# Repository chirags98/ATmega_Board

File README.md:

# ATmega_Board
This is a design to create a general purpose uC board using a ATmega328p microcontroller

Find the BOM (Bill of materials) on https://drive.google.com/open?id=1ma9ChhY5GpuYgg1Ucf6gE6C5UKoa5oTefCcq_7sxWGw

Find the Documentation of the board on https://drive.google.com/open?id=1ZgfvmyehAIBZDk0_nPWmhZg0xXYO81bvEzHlQfDXWbA

Find the example codes on https://github.com/chirags98/ATmega328-Example-Codes

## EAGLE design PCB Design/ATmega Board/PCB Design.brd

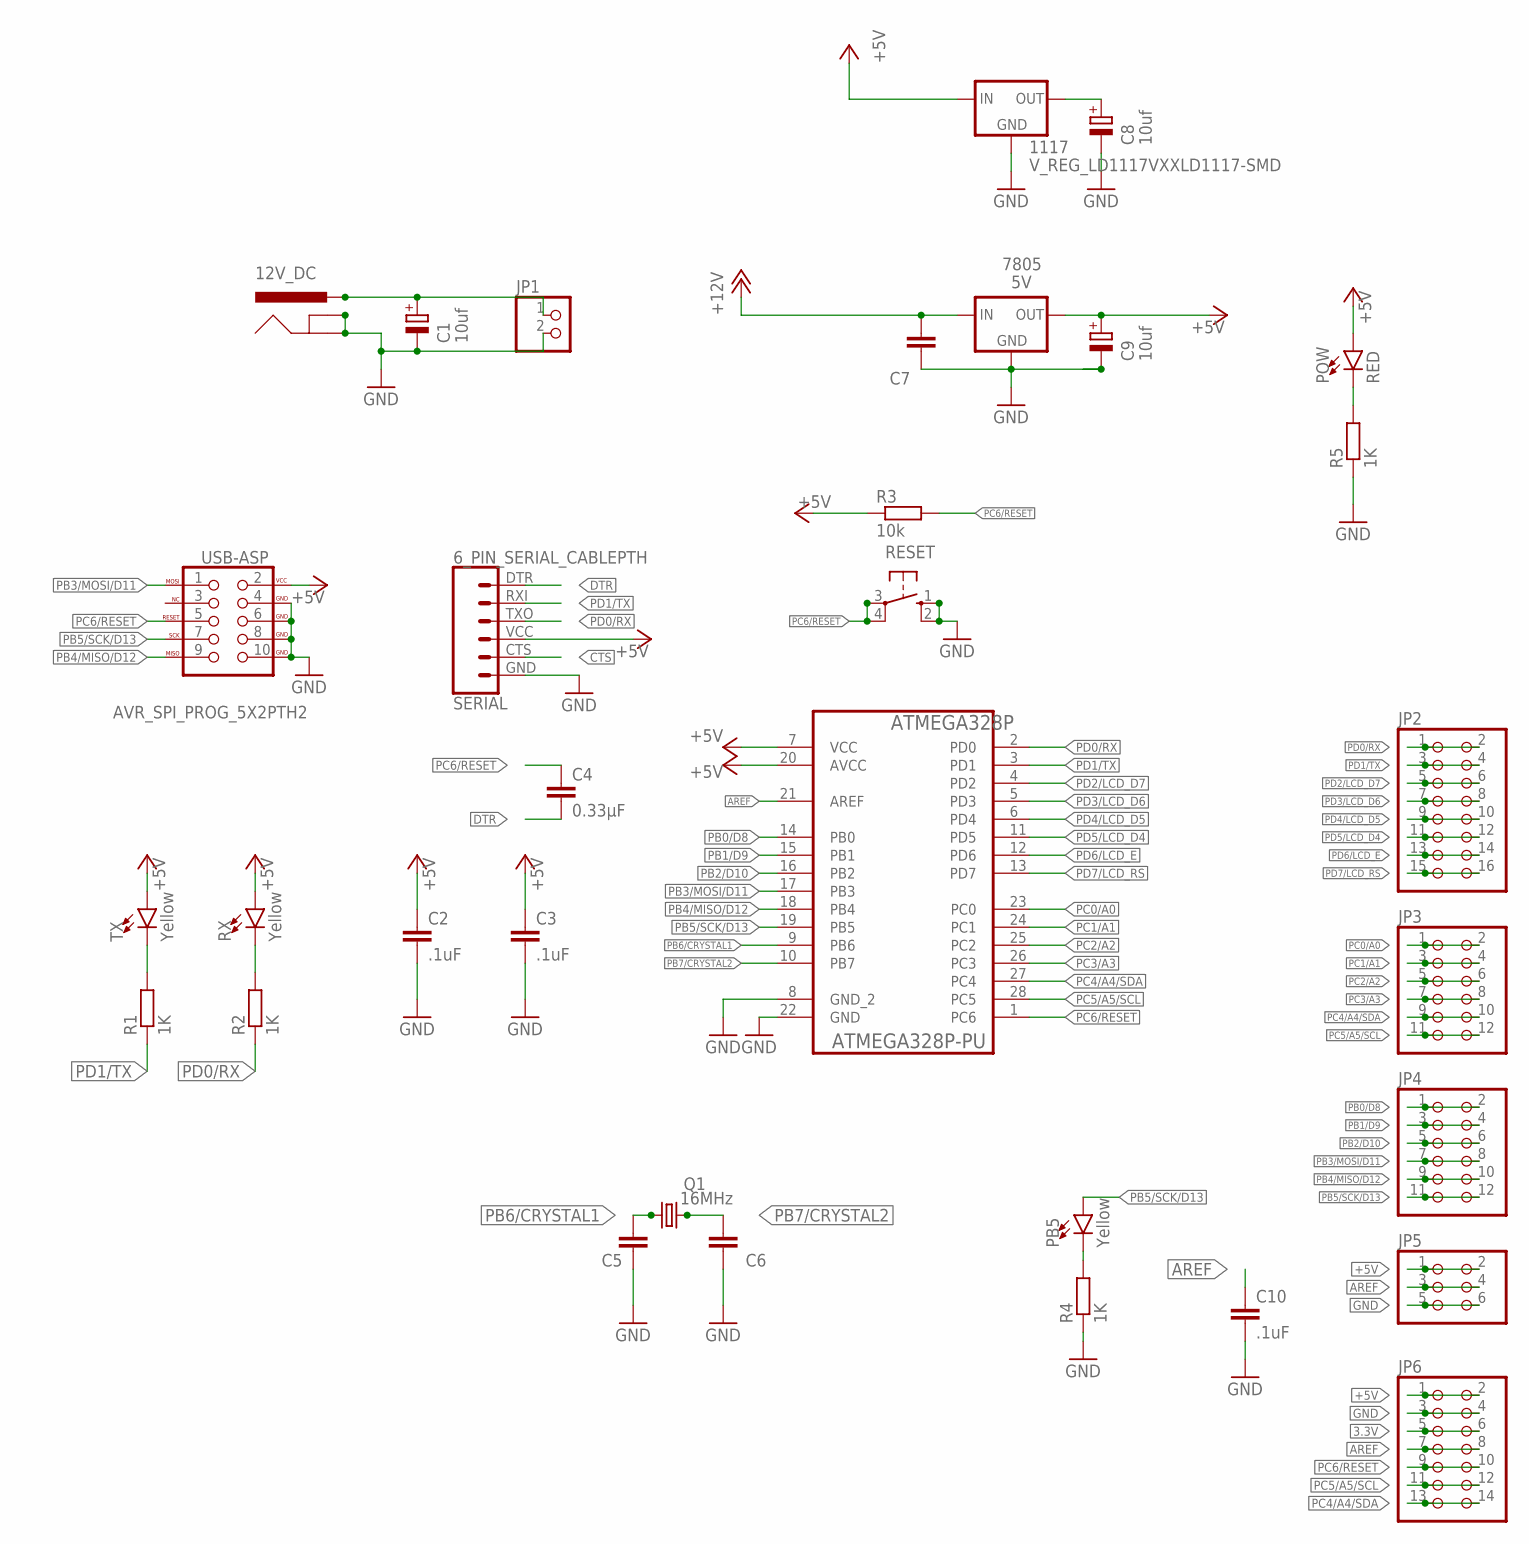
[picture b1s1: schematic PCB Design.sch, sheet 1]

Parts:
12V_DC: POWER_JACK; POWER_JACK_PTH; MPN SPC21365
1117: V_REG_LD1117VXXLD1117-SMD; SOT223
7805: 5V; TO-252
ATMEGA328P: ATMEGA328P-PU; DIP254P762X457-28
C1, C8, C9: 10uf; E2,5-6
C2, C3, C10: .1uF; C0805K
C4: 0.33µF; C0805K
C5, C6: 22pF; C0805K
C7: .1uf; C0805K
JP1: PINHD-1X2; 1X02
JP2: PINHD-2X8; 2X08
JP3, JP4: PINHD-2X6; 2X06
JP5: PINHD-2X3; 2X03
JP6: PINHD-2X7; 2X07
PB5: Yellow; LED-0603
POW: RED; LED-0603
Q1: 16MHz; HC49U70
R1, R2, R4, R5: 1K; M0805
R3: 10k; M0805
RESET: 10-XX; B3F-10XX
RX: Yellow; LED-0603
SERIAL: 6_PIN_SERIAL_CABLEPTH; FTDI_BASIC
TX: Yellow; LED-0603
USB-ASP: AVR_SPI_PROG_5X2PTH2; 2X5-SHROUDED

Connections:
3.3V: 1117.2 (OUT), C8.+, JP6.5, JP6.6
+5V: 1117.3 (IN), 7805.2 (OUT), ATMEGA328P.7 (VCC), ATMEGA328P.20 (AVCC), C2.1, C3.1, C9.+, JP5.1, JP5.2, JP6.1, JP6.2, POW.A, R3.1, RX.A, SERIAL.VCC (4), TX.A, USB-ASP.2 (VCC); also elsewhere on the board
+12V: 12V_DC.PWR, 7805.1 (IN), C1.+, C7.1, JP1.1
AREF: ATMEGA328P.21 (AREF), C10.1, JP5.3, JP5.4, JP6.7, JP6.8
CTS: SERIAL.CTS (5)
DTR: C4.2, SERIAL.DTR (1)
GND: 12V_DC.GND, 12V_DC.GNDBREAK, 1117.1 (GND), 7805.3 (GND), ATMEGA328P.8 (GND_2), ATMEGA328P.22 (GND), C1.-, C2.2, C3.2, C5.1, C6.1, C7.2, C8.-, C9.-, C10.2, JP1.2, JP5.5, JP5.6, JP6.3, JP6.4, R4.1, R5.1, RESET.1 (S), RESET.2 (S1), SERIAL.GND (6), USB-ASP.4 (GND), USB-ASP.6 (GND), USB-ASP.8 (GND), USB-ASP.10 (GND); also elsewhere on the board
unnamed: PB5.C, R4.2
unnamed: POW.C, R5.2
unnamed: R2.2, RX.C
unnamed: R1.2, TX.C
PB0/D8: ATMEGA328P.14 (PB0), JP4.1, JP4.2
PB1/D9: ATMEGA328P.15 (PB1), JP4.3, JP4.4
PB2/D10: ATMEGA328P.16 (PB2), JP4.5, JP4.6
PB3/MOSI/D11: ATMEGA328P.17 (PB3), JP4.7, JP4.8, USB-ASP.1 (MOSI)
PB4/MISO/D12: ATMEGA328P.18 (PB4), JP4.9, JP4.10, USB-ASP.9 (MISO)
PB5/SCK/D13: ATMEGA328P.19 (PB5), JP4.11, JP4.12, PB5.A, USB-ASP.7 (SCK)
PB6/CRYSTAL1: ATMEGA328P.9 (PB6), C5.2, Q1.1
PB7/CRYSTAL2: ATMEGA328P.10 (PB7), C6.2, Q1.2
PC0/A0: ATMEGA328P.23 (PC0), JP3.1, JP3.2
PC1/A1: ATMEGA328P.24 (PC1), JP3.3, JP3.4
PC2/A2: ATMEGA328P.25 (PC2), JP3.5, JP3.6
PC3/A3: ATMEGA328P.26 (PC3), JP3.7, JP3.8
PC4/A4/SDA: ATMEGA328P.27 (PC4), JP3.9, JP3.10, JP6.13, JP6.14
PC5/A5/SCL: ATMEGA328P.28 (PC5), JP3.11, JP3.12, JP6.11, JP6.12
PC6/RESET: ATMEGA328P.1 (PC6), C4.1, JP6.9, JP6.10, R3.2, RESET.3, RESET.4 (P1), USB-ASP.5 (RESET)
PD0/RX: ATMEGA328P.2 (PD0), JP2.1, JP2.2, R2.1, SERIAL.TXO (3)
PD1/TX: ATMEGA328P.3 (PD1), JP2.3, JP2.4, R1.1, SERIAL.RXI (2)
PD2/LCD_D7: ATMEGA328P.4 (PD2), JP2.5, JP2.6; also elsewhere on the board
PD3/LCD_D6: ATMEGA328P.5 (PD3), JP2.7, JP2.8; also elsewhere on the board
PD4/LCD_D5: ATMEGA328P.6 (PD4), JP2.9, JP2.10; also elsewhere on the board
PD5/LCD_D4: ATMEGA328P.11 (PD5), JP2.11, JP2.12; also elsewhere on the board
PD6/LCD_E: ATMEGA328P.12 (PD6), JP2.13, JP2.14; also elsewhere on the board
PD7/LCD_RS: ATMEGA328P.13 (PD7), JP2.15, JP2.16; also elsewhere on the board

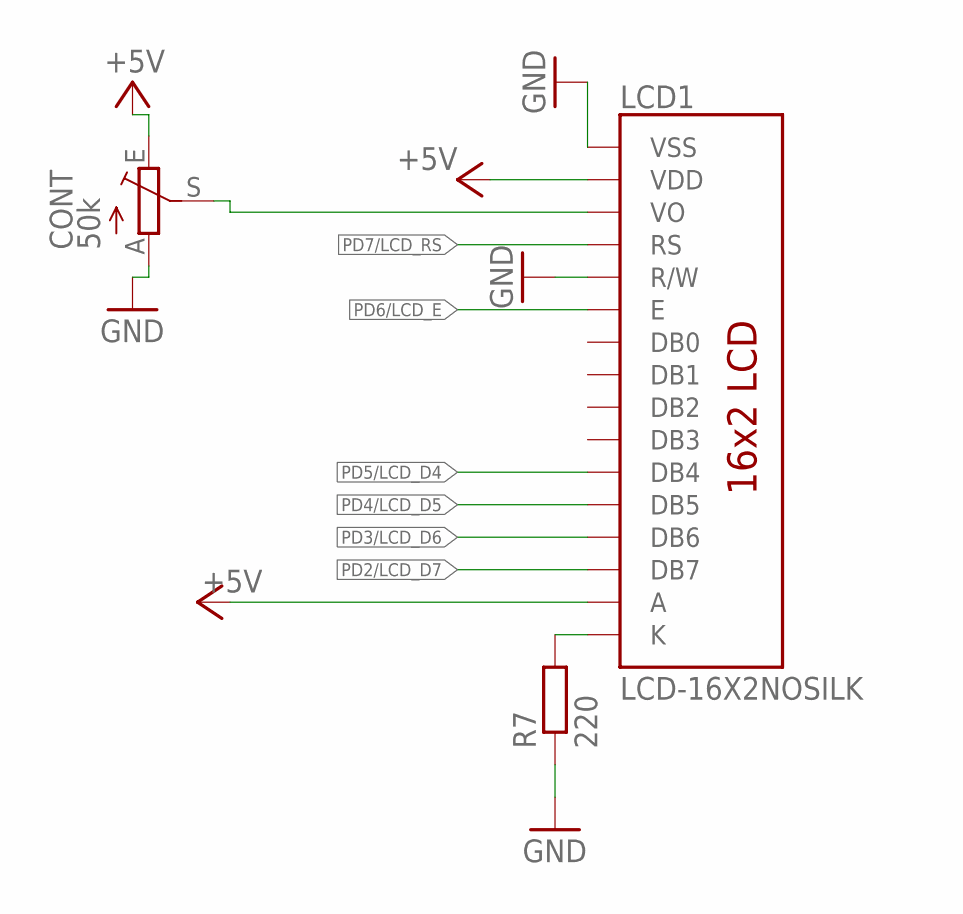
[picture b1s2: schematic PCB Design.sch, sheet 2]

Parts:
CONT: 50k; S64W
LCD1: LCD-16X2NOSILK; LCD-16X2_NOSILK
R7: 220; M0805

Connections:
+5V: CONT.E, LCD1.2 (VDD), LCD1.15 (A); also elsewhere on the board
GND: CONT.A, LCD1.1 (VSS), LCD1.5 (R/W), R7.1; also elsewhere on the board
unnamed: CONT.S, LCD1.3 (VO)
unnamed: LCD1.16 (K), R7.2
PD2/LCD_D7: LCD1.14 (DB7); also elsewhere on the board
PD3/LCD_D6: LCD1.13 (DB6); also elsewhere on the board
PD4/LCD_D5: LCD1.12 (DB5); also elsewhere on the board
PD5/LCD_D4: LCD1.11 (DB4); also elsewhere on the board
PD6/LCD_E: LCD1.6 (E); also elsewhere on the board
PD7/LCD_RS: LCD1.4 (RS); also elsewhere on the board

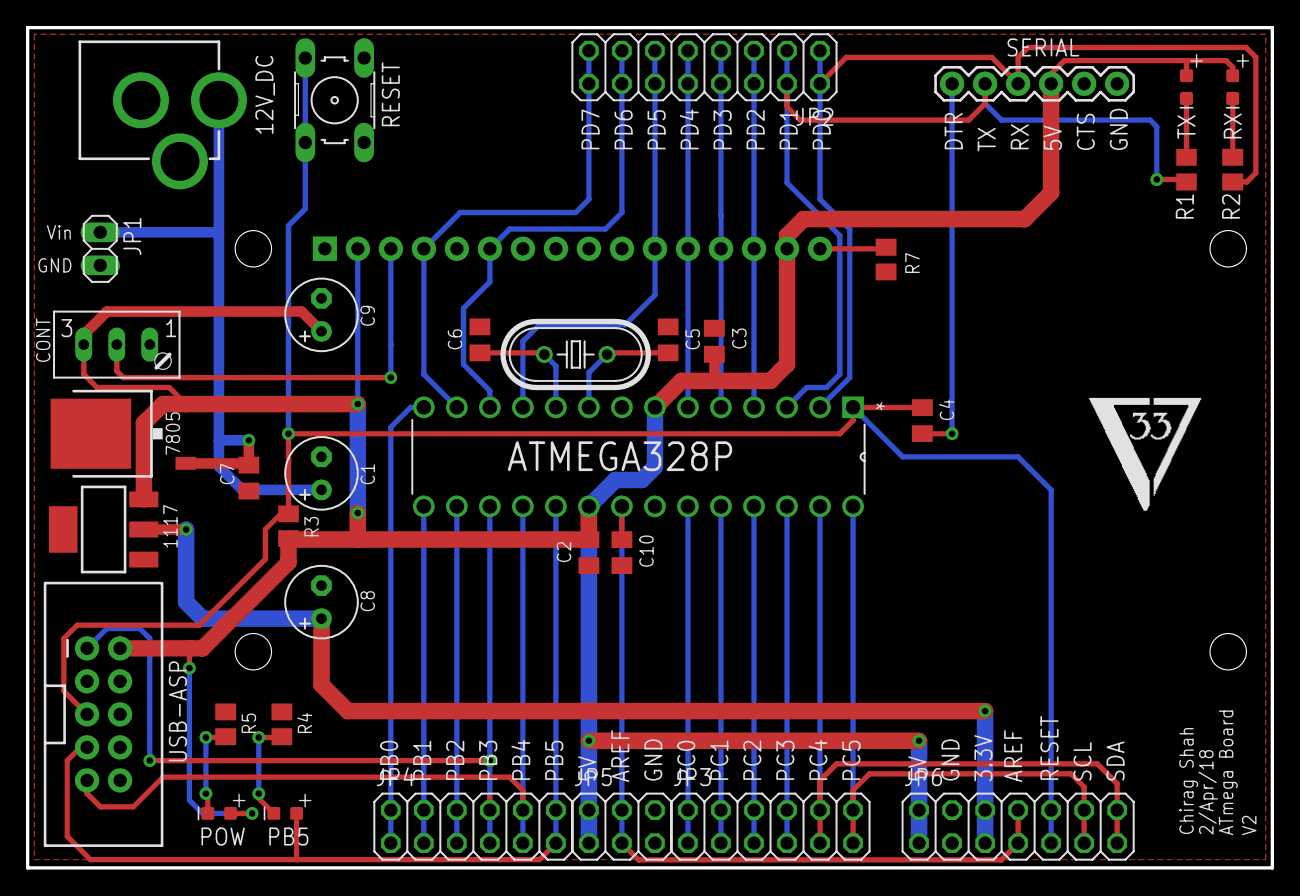
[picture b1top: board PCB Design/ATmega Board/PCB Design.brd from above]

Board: 2 copper layers, 95.8 x 64.6 mm, 36 parts (0 on the bottom side), 35 nets.

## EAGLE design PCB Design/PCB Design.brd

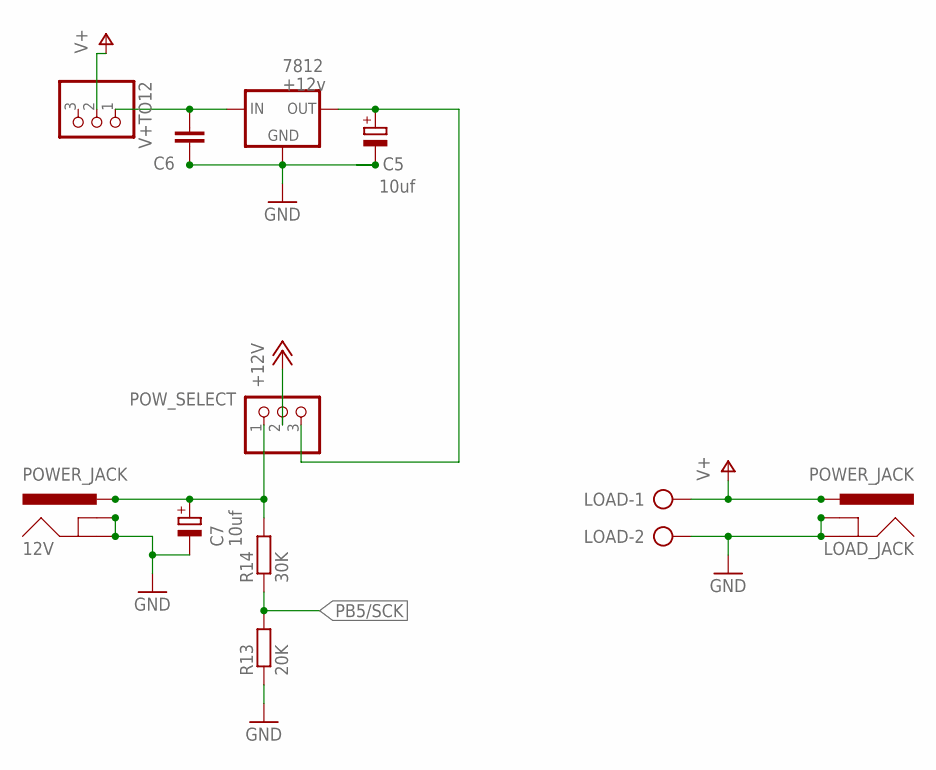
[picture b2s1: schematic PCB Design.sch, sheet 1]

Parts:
12V: POWER_JACK; POWER_JACK_PTH
7812: +12v; TO-252
C5, C7: 10uf; E2,5-6
C6: .1uF; C0805K
LOAD: AK500/2-H
LOAD_JACK: POWER_JACK; POWER_JACK_PTH
POW_SELECT: PINHD-1X3; 1X03
R13: 20K; M0805
R14: 30K; M0805
V+TO12: PINHD-1X3; 1X03

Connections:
12V_JACK_INPUT: 12V.PWR, C7.+, POW_SELECT.1, R14.2
12V_REG_O/P: 7812.2 (OUT), C5.+, POW_SELECT.3
+12V: POW_SELECT.2; also elsewhere on the board
GND: 12V.GND, 12V.GNDBREAK, 7812.3 (GND), C5.-, C6.2, C7.-, LOAD.2, LOAD_JACK.GND, LOAD_JACK.GNDBREAK, R13.1; also elsewhere on the board
unnamed: 7812.1 (IN), C6.1, V+TO12.1
PB5/SCK: R13.2, R14.1; also elsewhere on the board
V+: LOAD.1, LOAD_JACK.PWR, V+TO12.2

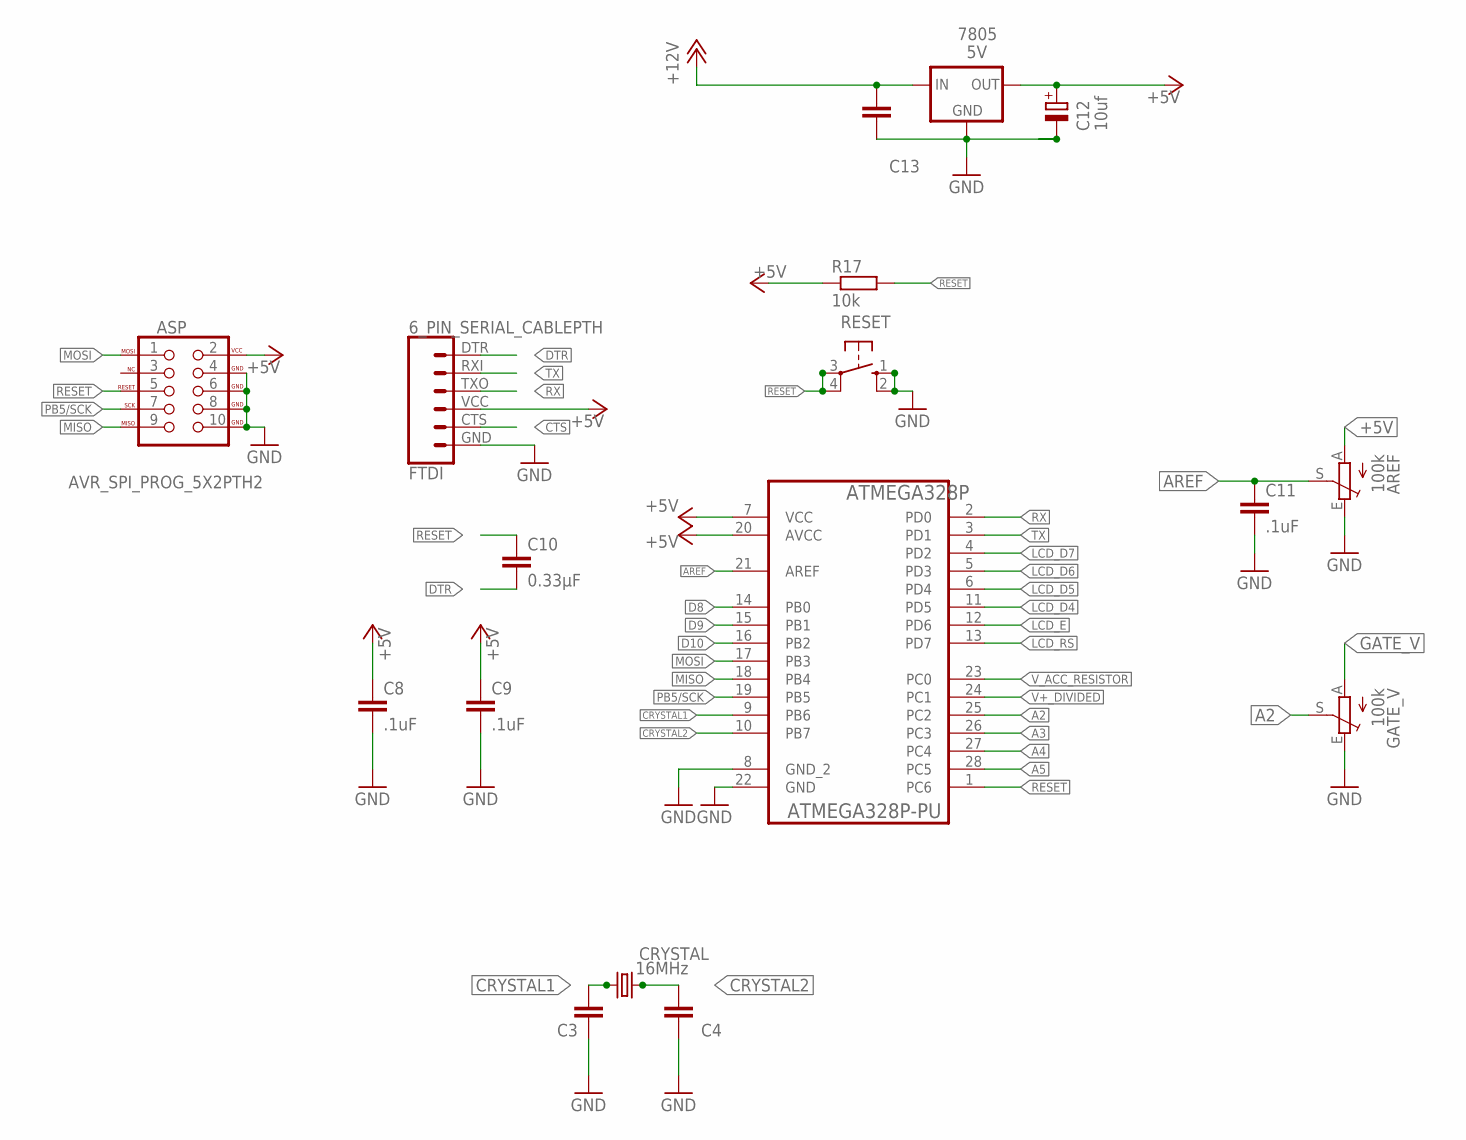
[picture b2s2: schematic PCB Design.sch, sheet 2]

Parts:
7805: 5V; TO-252
AREF: 100k; S64W
ASP: AVR_SPI_PROG_5X2PTH2; 2X5-SHROUDED
ATMEGA328P: ATMEGA328P-PU; DIP254P762X457-28
C3, C4: 22pF; C0805K
C8, C9, C11: .1uF; C0805K
C10: 0.33µF; C0805K
C12: 10uf; E2,5-6
C13: .1uf; C0805K
CRYSTAL: 16MHz; HC49U70
FTDI: 6_PIN_SERIAL_CABLEPTH; FTDI_BASIC
GATE_V: 100k; S64W
R17: 10k; M0805
RESET: 10-XX; B3F-10XX

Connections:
+5V: 7805.2 (OUT), AREF.A, ASP.2 (VCC), ATMEGA328P.7 (VCC), ATMEGA328P.20 (AVCC), C8.1, C9.1, C12.+, FTDI.VCC (4), R17.1; also elsewhere on the board
+12V: 7805.1 (IN), C13.1; also elsewhere on the board
A2: ATMEGA328P.25 (PC2), GATE_V.S
A3: ATMEGA328P.26 (PC3)
A4: ATMEGA328P.27 (PC4)
A5: ATMEGA328P.28 (PC5)
AREF: AREF.S, ATMEGA328P.21 (AREF), C11.1
CRYSTAL1: ATMEGA328P.9 (PB6), C3.2, CRYSTAL.1
CRYSTAL2: ATMEGA328P.10 (PB7), C4.2, CRYSTAL.2
CTS: FTDI.CTS (5)
D8: ATMEGA328P.14 (PB0)
D9: ATMEGA328P.15 (PB1)
D10: ATMEGA328P.16 (PB2)
DTR: C10.2, FTDI.DTR (1)
GATE_V: GATE_V.A
GND: 7805.3 (GND), AREF.E, ASP.4 (GND), ASP.6 (GND), ASP.8 (GND), ASP.10 (GND), ATMEGA328P.8 (GND_2), ATMEGA328P.22 (GND), C3.1, C4.1, C8.2, C9.2, C11.2, C12.-, C13.2, FTDI.GND (6), GATE_V.E, RESET.1 (S), RESET.2 (S1); also elsewhere on the board
LCD_D4: ATMEGA328P.11 (PD5); also elsewhere on the board
LCD_D5: ATMEGA328P.6 (PD4); also elsewhere on the board
LCD_D6: ATMEGA328P.5 (PD3); also elsewhere on the board
LCD_D7: ATMEGA328P.4 (PD2); also elsewhere on the board
LCD_E: ATMEGA328P.12 (PD6); also elsewhere on the board
LCD_RS: ATMEGA328P.13 (PD7); also elsewhere on the board
MISO: ASP.9 (MISO), ATMEGA328P.18 (PB4)
MOSI: ASP.1 (MOSI), ATMEGA328P.17 (PB3)
PB5/SCK: ASP.7 (SCK), ATMEGA328P.19 (PB5); also elsewhere on the board
RESET: ASP.5 (RESET), ATMEGA328P.1 (PC6), C10.1, R17.2, RESET.3, RESET.4 (P1)
RX: ATMEGA328P.2 (PD0), FTDI.TXO (3)
TX: ATMEGA328P.3 (PD1), FTDI.RXI (2)
V+_DIVIDED: ATMEGA328P.24 (PC1)
V_ACC_RESISTOR: ATMEGA328P.23 (PC0)

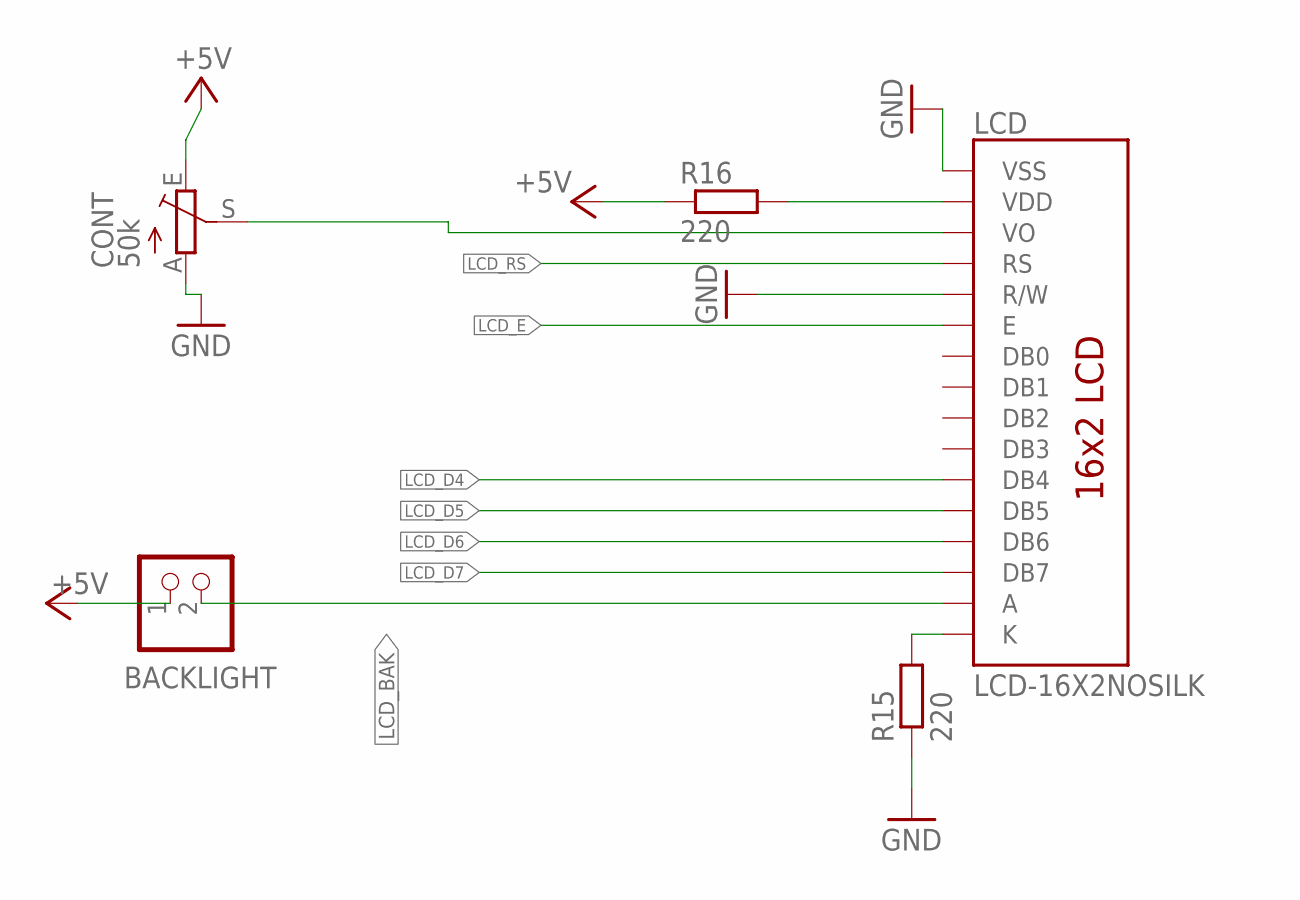
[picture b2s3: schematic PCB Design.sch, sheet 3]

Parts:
BACKLIGHT: PINHD-1X2; 1X02
CONT: 50k; S64W
LCD: LCD-16X2NOSILK; LCD-16X2_NOSILK
R15, R16: 220; M0805

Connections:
+5V: BACKLIGHT.1, CONT.E, R16.1; also elsewhere on the board
GND: CONT.A, LCD.1 (VSS), LCD.5 (R/W), R15.1; also elsewhere on the board
LCD_BAK: BACKLIGHT.2, LCD.15 (A)
LCD_D4: LCD.11 (DB4); also elsewhere on the board
LCD_D5: LCD.12 (DB5); also elsewhere on the board
LCD_D6: LCD.13 (DB6); also elsewhere on the board
LCD_D7: LCD.14 (DB7); also elsewhere on the board
LCD_E: LCD.6 (E); also elsewhere on the board
LCD_RS: LCD.4 (RS); also elsewhere on the board
unnamed: CONT.S, LCD.3 (VO)
unnamed: LCD.2 (VDD), R16.2
unnamed: LCD.16 (K), R15.2

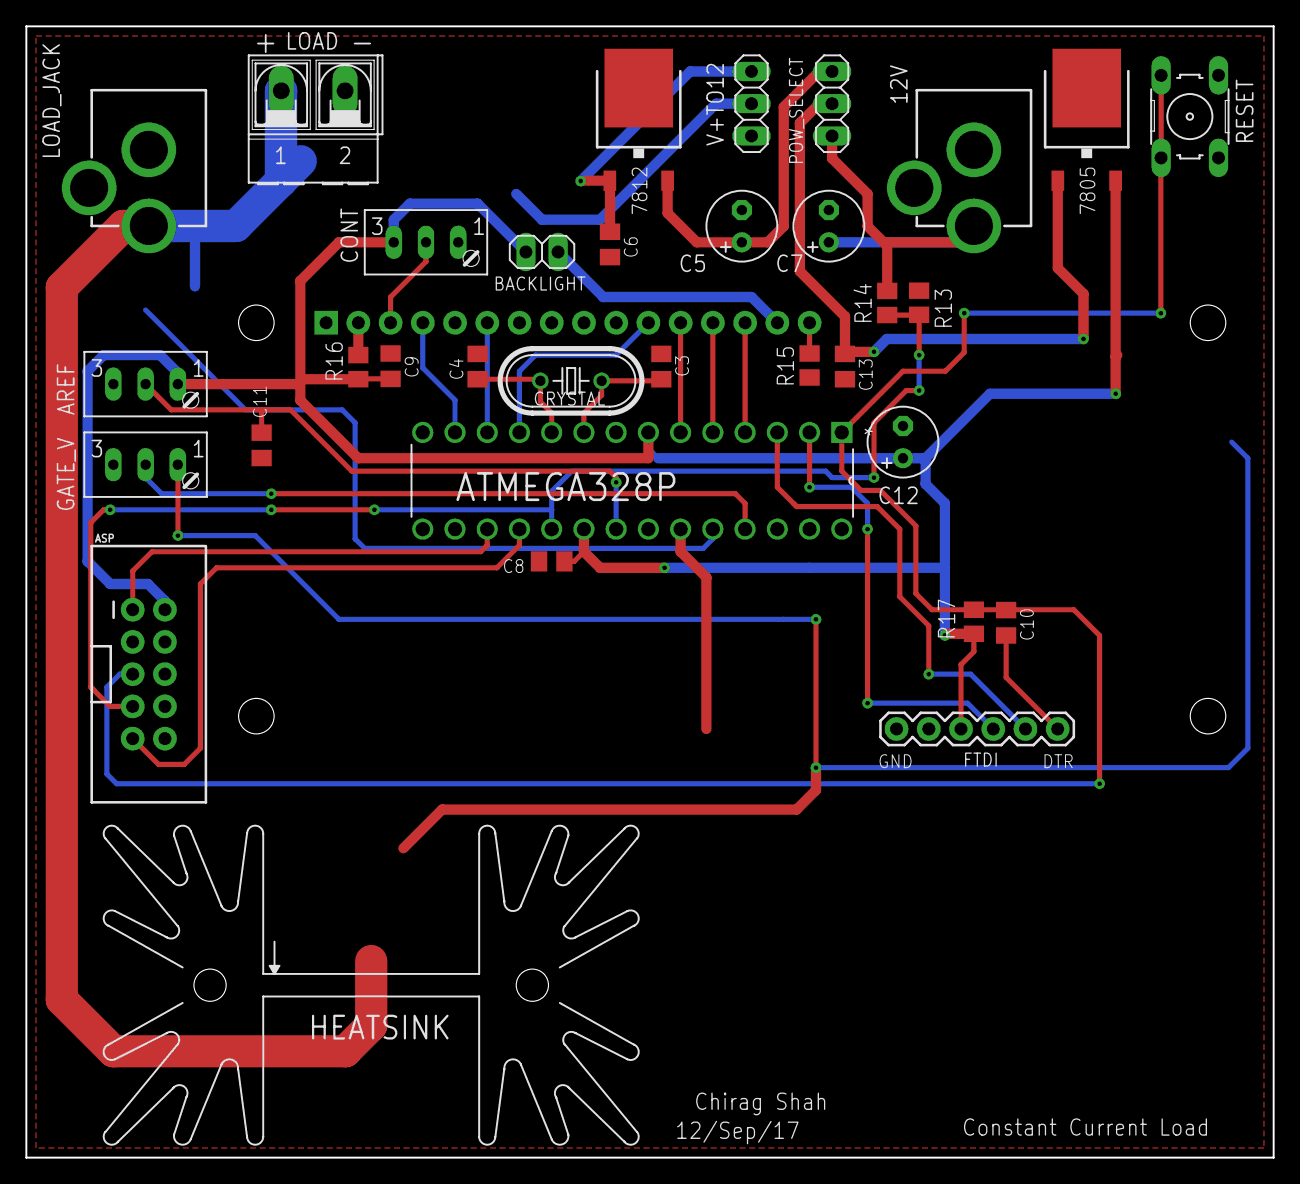
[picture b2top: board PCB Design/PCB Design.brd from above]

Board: 2 copper layers, 98.3 x 89.2 mm, 34 parts (0 on the bottom side), 28 nets.

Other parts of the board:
HEATSINK: SK129-HOLE

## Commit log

2018-02-16 Made a folder for the PCB design and copied CCL design
2018-02-16 Working on design
2018-02-20 testing new branch
2018-02-20 worked on double sided board
2018-02-24 Worked on routing and silkscreen
2018-02-24 Before routing 3.3v reg
2018-02-24 Before moving pin header
2018-02-24 Done
2018-02-24 Corrected mistake and generated gerbers
2018-02-26 Verified schematic
2018-02-27 Before renumbering parts
2018-02-27 Final
2018-03-26 Corrected Silkscreen
2018-04-02 Corrected mistakes, V2, Final
2018-04-02 Zipped Final Gerbers
2018-04-08 Added BOM and updated Readme
2018-04-08 Added reference photographs
2018-06-08 added documentation
2019-05-12 Updated Documentation

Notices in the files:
parts and their libraries:
SparkFun-Connectors: Licensing: Creative Commons ShareAlike 4.0 International - https://creativecommons.org/licenses/by-sa/4.0
